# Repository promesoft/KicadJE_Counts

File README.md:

# KicadJE_Counts
Counter module as a successor to EU-3

# Purpose
## Count
10 step counter

Input +/- 10V DC
 - Clock  
 - Hold
 - Reset

Output +/- 10V DC x 10
 - Steps
 - Clock

Adjustment
 - Frequency
 - Hold

## Dist Two
Input +/- 10V DC
 - signal

Output +/- 10V DC
 - signal

Adjustment:
 - Distortion/gain section 1 (ch 1+2) feedback dist
 - Distortion/gain section 2 (ch 1+2) output stage dist + pos LED to GND

# Status - in the mail
## Initial 
| Stage  | Detail | Status |
| ------------- | ------------- | ------------- |
| create material  | sch | ok |
| | pcb | ok |
| | gerber | ok |
| production  |   | ok |
|  | produced | ok |
|  | delivered | in the mail |
## Preliminary validation
| Test  | Detail | Status |
| ------------- | ------------- | ------------- |
| Initial Inspection | | OK |
| Initial Technical Test | Counts |  |
| Initial Technical Test | Dist Two | OK - all pots are reversed - LED should be moved to the free spot between input and outputs |
| Initial Product Test | Counts |  |
| Initial Product Test | Dist Two | Distorts - one channel more than the other - one input splits in two - default component values gives a lot or a little distortion |

## Secondary validation
| Test  | Detail | Status |
| ------------- | ------------- |------------- |
| Product Test | Counts | |
| Product Test | Dist Two | |
| Quality | Counts | |
| Quality | Dist Two | |
| Long Term Product Test |  |  |
| Power Draw |  | 

## Errata
### Errata - Dist Two
* all pots are reversed
* default component values gives a lot or a little distortion

## Issues and Notes
### 

# Pictures

# Schematic
## Counts

## Dist Two

# Analysis
## Counts

## Prototype

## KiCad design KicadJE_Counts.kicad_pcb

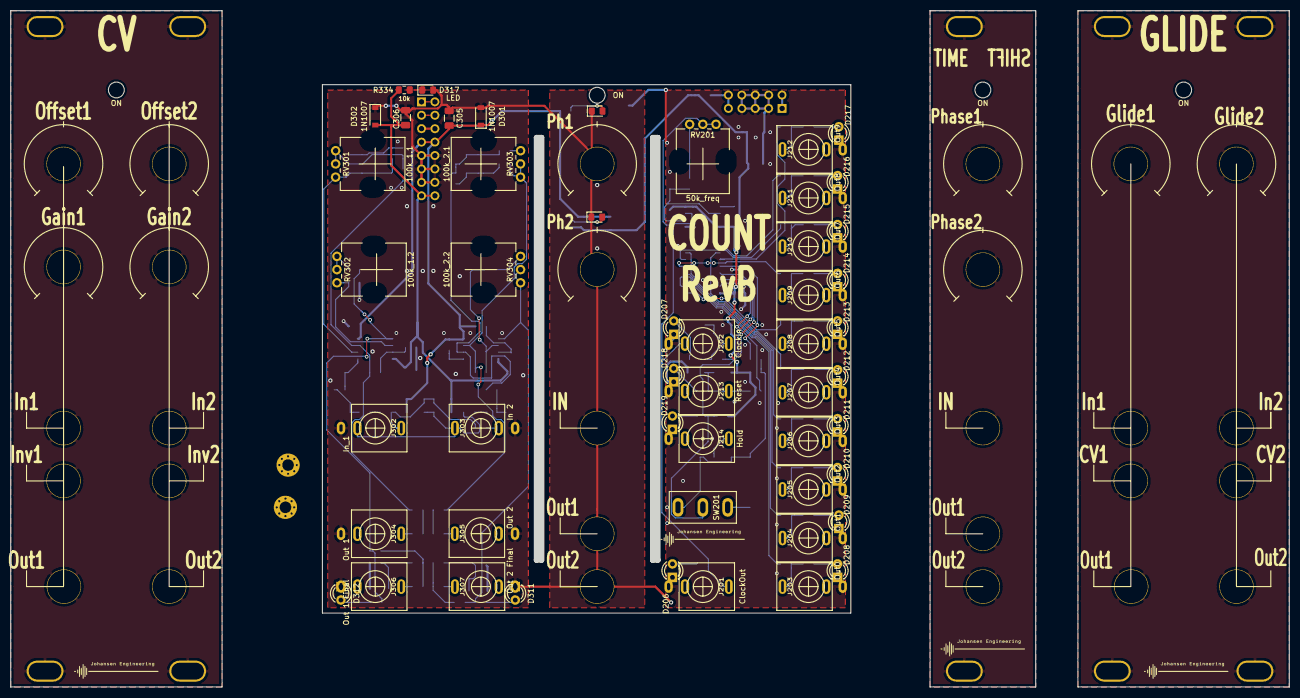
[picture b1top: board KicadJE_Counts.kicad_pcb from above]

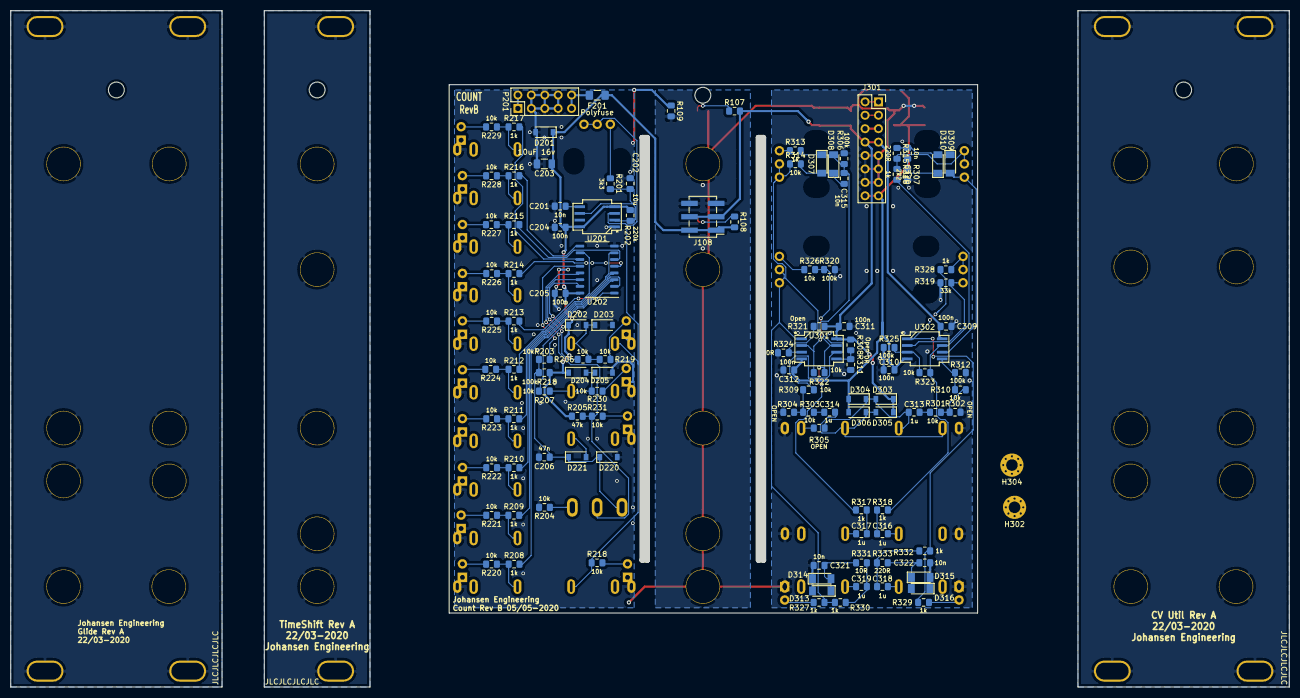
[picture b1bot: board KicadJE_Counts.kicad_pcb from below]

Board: 2 copper layers, 100.0 x 100.0 mm, 209 parts (122 on the bottom side), 97 nets.

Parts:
C201, C315, C320, C321, C322: 10n; C_0805_AJ
C202: 10u; C_0805_AJ
C203: 10uF 16v; C_1206_3216Metric
C204, C205, C309, C310, C311, C312: 100n; C_0805_AJ
C206: 47n; C_0805_AJ
C305, C306: 100uF 16v; C_1206_3216Metric
C313, C314, C316, C317, C318, C319: 1u; C_0805_AJ
D101, D102: D_LED; LED_0805_2012Metric_Pad1.15x1.40mm_HandSolder
D201, D301, D302, D303, D304, D305, D306: 1N1007; D_SOD-123
D202, D203, D204, D205: 1N5819; D_SOD-123
D206: LED_Clk_Out; LED_D3.0mm
D207: LED_Clk_In; LED_D3.0mm
D208: LED_0; LED_D3.0mm
D209: LED_1; LED_D3.0mm
D210: LED_2; LED_D3.0mm
D211: LED_3; LED_D3.0mm
D212: LED_4; LED_D3.0mm
D213: LED_5; LED_D3.0mm
D214: LED_6; LED_D3.0mm
D215: LED_7; LED_D3.0mm
D216: LED_8; LED_D3.0mm
D217: LED_9; LED_D3.0mm
D218: LED_RST; LED_D3.0mm
D219: LED_HLD; LED_D3.0mm
D220: 1N4007; D_SOD-123
D221: 1N4148; D_SOD-123
D307, D308, D309, D310, D313, D314, D315, D316: LL4148; D_MiniMELF
D311, D312: LED; LED_D3.0mm
D317: LED; LED_0805_2012Metric_Pad1.15x1.40mm_HandSolder
F201: Polyfuse; Fuse_1206_3216Metric_Pad1.42x1.75mm_HandSolder
H101, H101#2, H301, H301#2: ON; LED_Hole_3mm
H102, H102#2, H102#3, H103, H103#2, H103#3, H104, H104#2, H105, H105#2: MountingHole_Pad; MountingHole_Eurorack3
H302, H304: 2,2mm; MountingHole_2.2mm_M2_Pad_Via
J108: Conn_02x03_Male; PinHeader_2x03_P2.54mm_Vertical_SMD
J201: ClockOut; PJ301SM
J202: ClockIn; PJ301SM
J203: Out0; PJ301SM
J204: Out1; PJ301SM
J205: Out2; PJ301SM
J206: Out3; PJ301SM
J207: Out4; PJ301SM
J208: Out5; PJ301SM
J209: Out6; PJ301SM
J210: Out7; PJ301SM
J211: Out8; PJ301SM
J212: Out9; PJ301SM
J213: Reset; PJ301SM
J214: Hold; PJ301SM
J301: Doepfer connector; PinSocket_2x08_P2.54mm_Vertical
J302: In_1; PJ301SM
J303: In 2; PJ301SM
J304: Out 1; PJ301SM
J305: Out 2; PJ301SM
J306: Out 1 Final; PJ301SM
J307: Out 2 Final; PJ301SM
P201: HEADER_2x5_Doepfer; PinHeader_2x05_P2.54mm_Vertical
R107, R108, R109: DNP; R_0805_AJ
R201: 3k3; R_0805_AJ
R202: 220k; R_0805_AJ
R203, R204, R206, R207, R218#2, R219, R220, R221, R222, R223, R224, R225, R226, R227, R228, R229, R230, R231, R301, R303, R309, R310, R314, R322, R323, R326, R334: 10k; R_0805_AJ
R205: 47k; R_0805_AJ
R208, R209, R210, R211, R212, R213, R214, R215, R216, R217, R313, R316, R317, R318, R327, R328, R329, R330, R332: 1k; R_0805_AJ
R218, R306, R312, R320, R325: 100k; R_0805_AJ
R302, R304, R305: OPEN; R_0805_AJ
R307: 2k2; R_0805_AJ
R308, R321: Open; R_0805_AJ
R311, R324: 0R; R_0805_AJ
R315, R333: 220R; R_0805_AJ
R319: 33k; R_0805_AJ
R331: 10R; R_0805_AJ
RV201: 50k_freq; Potentiometer_China_RK09_Single_Vertical_AJ
RV301: 100k_1.1; Potentiometer_China_RK09_Single_Vertical_AJ
RV302: 100k_1.2; Potentiometer_China_RK09_Single_Vertical_AJ
RV303: 100k_2.1; Potentiometer_China_RK09_Single_Vertical_AJ
RV304: 100k_2.2; Potentiometer_China_RK09_Single_Vertical_AJ
SW201: Run; SP1MS1
TP102, TP102#2, TP303, TP303#2: SQ; Jack_6m3
TP103, TP103#2, TP301, TP301#2: In1; Jack_6m3
TP105, TP105#2: In3; Jack_6m3
TP106, TP106#2: HS; Jack_6m3
TP107, TP107#2, TP107#5: OFF1; Pot_6m3_scale1
TP107#3, TP107#4: FM; Jack_6m3
TP108, TP108#2: PWM; Jack_6m3
TP112, TP112#2, TP112#3: Fine; Pot_6m3_scale1
TP302, TP302#2: Tri; Jack_6m3
TP304, TP304#2: PWM1; Pot_6m3_scale1
TP305, TP305#2: PWM2; Pot_6m3_scale1
U201: LM555; AJ_SO-8_5.3x6.2mm_P1.27mm
U202: 4017; SOIC-16_4.55x10.3mm_P1.27mm
U301, U302: TL072; AJ_SO-8_5.3x6.2mm_P1.27mm

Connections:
+5V: J301.5, J301.6
+12V: C305.1, C309.2, C311.2, D301.1, D303.1, D305.1, J108.3, J108.4, J301.7, J301.8, R107.2, R308.2, R321.2, U301.8, U302.8
+12Vc: C203.1, C204.2, C205.2, D201.1, D202.1, D204.1, F201.2, J108.1, J108.2, R108.2, R202.1, R205.1, R218.1, U201.4, U201.8, U202.16
-12V: C306.2, C310.1, C312.1, D302.2, D304.2, D306.2, J301.15, J301.16, R334.1, U301.4, U302.4
/KicadJE_Counts2/CV: J301.3, J301.4
/KicadJE_Counts2/Gate: J301.1, J301.2
/KicadJE_Counts3/+12: F201.1, P201.9, P201.10
/KicadJE_Counts3/-12: P201.1, P201.2
ClockIn: D202.2, D203.1, J202.T, R206.2, R219.1
ClockOut: J201.T, J202.TN, R218#2.1, RV201.2, RV201.3, U201.3
GND: C305.2, C306.1, C309.1, C310.2, C311.1, C312.2, C321.2, C322.2, D101.1, D102.1, D301.2, D302.1, D311.1, D312.1, D313.2, D314.1, D315.2, D316.1, D317.2, H102.1, H102#2.1, H102#3.1, H103.1, H103#2.1, H103#3.1, H104.1, H104#2.1, H105.1, H105#2.1, J108.5, J108.6, J301.9, J301.10, J301.11, J301.12, J301.13, J301.14, J302.S, J303.S, J304.S, J305.S, J306.S, J307.S, R109.2, R302.2, R304.2, R306.2, R307.2, R311.1, R312.1, R319.2, R320.2, R324.1, R325.1, TP102.1, TP102#2.1, TP103.1, TP103#2.1, TP105.1, TP105#2.1, TP106.1, TP106#2.1, TP107.1, TP107#2.1, TP107#3.1, TP107#4.1, TP107#5.1, TP108.1, TP108#2.1, TP112.1, TP112#2.1, TP112#3.1, TP301.1, TP301#2.1, TP302.1, TP302#2.1, TP303.1, TP303#2.1, TP304.1, TP304#2.1, TP305.1, TP305#2.1
GNDS: C201.1, C202.2, C203.2, C204.1, C205.1, C206.2, D201.2, D203.2, D205.2, D206.1, D207.1, D208.1, D209.1, D210.1, D211.1, D212.1, D213.1, D214.1, D215.1, D216.1, D217.1, D218.1, D219.1, D220.2, J201.S, J202.S, J203.S, J204.S, J205.S, J206.S, J207.S, J208.S, J209.S, J210.S, J211.S, J212.S, J213.S, J214.S, P201.3, P201.4, P201.5, P201.6, P201.7, P201.8, R109.1, R204.2, U201.1, U202.8
Hold: C206.1, D220.1, D221.1, R203.2, R218.2, SW201.3
In_1: R301.2, R302.1, R310.2
In_2: R303.2, R304.1, R309.2
unnamed: C201.2, U201.5
unnamed: C202.1, R201.2, R202.2, U201.2, U201.6
unnamed: C313.1, D303.2, D304.1, J302.T, R305.1
unnamed: C313.2, R301.1
unnamed: C314.1, D305.2, D306.1, J302.TN, J303.T
unnamed: C314.2, R303.1
unnamed: C315.1, D307.2, D308.1, R306.1, R309.1, R313.2, U301.6
unnamed: C315.2, D307.1, D308.2, R314.2
unnamed: C316.1, J304.T
unnamed: C317.1, J305.T
unnamed: C318.1, J306.T
unnamed: C319.1, J307.T
unnamed: C320.2, D309.1, D310.2, R315.1
unnamed: C321.1, D313.1, D314.2, R331.1
unnamed: C322.1, D315.1, D316.2, R333.1
unnamed: D101.2, R107.1
unnamed: D102.2, R108.1
unnamed: D206.2, R218#2.2
unnamed: D207.2, R219.2
unnamed: D208.2, R220.2
unnamed: D209.2, R221.2
unnamed: D210.2, R222.2
unnamed: D211.2, R223.2
unnamed: D212.2, R224.2
unnamed: D213.2, R225.2
unnamed: D214.2, R226.2
unnamed: D215.2, R227.2
unnamed: D216.2, R228.2
unnamed: D217.2, R229.2
unnamed: D218.2, R230.2
unnamed: D219.2, R231.2
unnamed: D221.2, J214.T
unnamed: D311.2, R327.1
unnamed: D312.2, R329.1
unnamed: D317.1, R334.2
unnamed: J303.TN, R305.2
unnamed: R201.1, RV201.1
unnamed: R204.1, SW201.1
unnamed: R205.2, R231.1, SW201.2, U202.13
unnamed: R206.1, U202.14
unnamed: R207.1, U202.15
unnamed: R208.2, U202.3
unnamed: R209.2, U202.2
unnamed: R210.2, U202.4
unnamed: R211.2, U202.7
unnamed: R212.2, U202.10
unnamed: R213.2, U202.1
unnamed: R214.2, U202.5
unnamed: R215.2, U202.6
unnamed: R216.2, U202.9
unnamed: R217.2, U202.11
unnamed: R308.1, R311.2, U301.5
unnamed: R310.1, R312.2, U302.5
unnamed: R316.2, R318.1, R323.2, U302.7
unnamed: R320.1, R322.1, R326.2, U301.2
unnamed: R321.1, R324.2, U301.3
unnamed: R323.1, R325.2, U302.3
unnamed: R328.2, R329.2, R332.2, U302.1
Out0: J203.T, R208.1, R220.1
Out1: J204.T, R209.1, R221.1
Out1_Dist: C316.2, R318.2
Out1_Final: C318.2, R332.1, R333.2
Out2: J205.T, R210.1, R222.1
Out2_Dist: C317.2, R317.2
Out2_Final: C319.2, R330.1, R331.2
Out3: J206.T, R211.1, R223.1
Out4: J207.T, R212.1, R224.1
Out5: J208.T, R213.1, R225.1
Out6: J209.T, R214.1, R226.1
Out7: J210.T, R215.1, R227.1
Out8: J211.T, R216.1, R228.1
Out9: J212.T, R217.1, R229.1
OutCarry: R203.1, U202.12
POT1_C: R315.2, R316.1, RV301.2, RV301.3
POT1_L: C320.1, D309.2, D310.1, R307.1, RV301.1, U302.6
POT2_C: R328.1, RV302.2, RV302.3
POT2_L: R319.1, RV302.1, U302.2
POT3_C: R314.1, R317.1, R322.2, RV303.2, RV303.3, U301.7
POT3_L: R313.1, RV303.1
POT4_C: R327.2, R330.2, RV304.2, RV304.3, U301.1
POT4_L: R326.1, RV304.1
Reset: D204.2, D205.1, J213.T, R207.2, R230.1

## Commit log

2020-04-30 counter fine
2020-05-02 distortion added as count2
2020-05-04 Clk I/O
2020-05-04 sch updates
2020-05-04 footprint updates
2020-05-04 major components placed for counter
2020-05-05 Count routed w component labels
2020-05-05 Update KicadJE_Counts.kicad_pcb
    Count labels
2020-05-18 Update KicadJE_Counts2.sch
    Dummy diode light
2020-05-18 Update KicadJE_Counts.sch
    GND conn
2020-05-18 Update KicadJE_Counts.kicad_pcb
    LED and GND on center panel
2020-05-18 Update KicadJE_Counts.sch
    conn for led
2020-05-18 change header pin out
2020-05-18 cleanup old conn
2020-05-18 Update KicadJE_Counts.kicad_pcb
    input circuit
2020-05-18 Update KicadJE_Counts2.sch
    conn pots
2020-05-18 Changed label types for POT's
2020-05-19 Update KicadJE_Counts.kicad_pcb
    components placed
2020-05-19 Update KicadJE_Counts.kicad_pcb
    wired
2020-05-19 Update KicadJE_Counts.kicad_pcb
    DRC
2020-05-19 PCB Labels
2020-05-19 Gerber
